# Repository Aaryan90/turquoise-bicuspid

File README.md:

TurquoiseBicuspid
=================

Bluetooth Notification System

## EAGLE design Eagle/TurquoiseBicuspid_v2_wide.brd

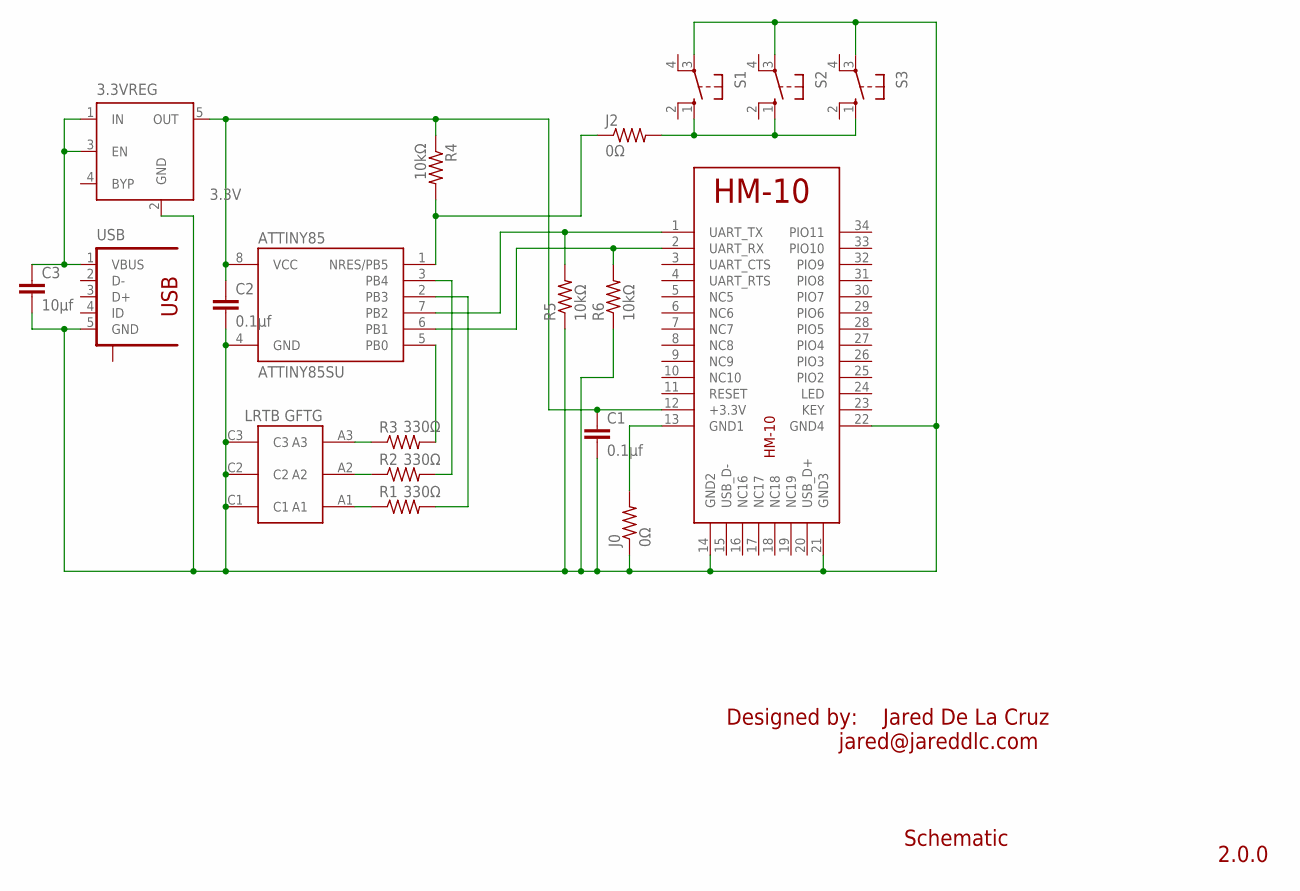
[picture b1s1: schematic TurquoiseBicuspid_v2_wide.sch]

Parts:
3.3VREG: 3.3V; SOT23-5
ATTINY85: ATTINY85SU; ATTINY85
C1, C2: 0.1µf; C1206
C3: 10µf; C1206
HM-10: HM-10BOARD; HM-10
J0, J2: 0Ω; R1206
R1, R2, R3: 330Ω; M1206
R4, R5, R6: 10kΩ; R1206
S1, S2, S3: 10-XX; B3F-10XX
U$1: LRTB_GFTG
USB: 10118192-0001LF

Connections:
3.3V: 3.3VREG.5 (OUT), ATTINY85.8 (VCC), C1.1, C2.1, HM-10.12 (+3.3V), R4.1
5V: 3.3VREG.1 (IN), 3.3VREG.3 (EN), C3.1, USB.1 (VBUS)
A1: ATTINY85.2 (PB3), R1.1, R1.2, U$1.A1
A2: ATTINY85.3 (PB4), R2.1, R2.2, U$1.A2
A3: ATTINY85.5 (PB0), R3.1, R3.2, U$1.A3
BT_RX: ATTINY85.6 (PB1), HM-10.2 (UART_RX), R6.2
BT_TX: ATTINY85.7 (PB2), HM-10.1 (UART_TX), R5.2
GND: 3.3VREG.2 (GND), ATTINY85.4 (GND), C1.2, C2.2, C3.2, HM-10.13 (GND1), HM-10.14 (GND2), HM-10.21 (GND3), HM-10.22 (GND4), J0.1, J0.2, R5.1, R6.1, S1.3, S2.3, S3.3, U$1.C1, U$1.C2, U$1.C3, USB.5 (GND)
RESET: ATTINY85.1 (NRES/PB5), J2.1, J2.2, R4.2, S1.1 (S), S2.1 (S), S3.1 (S)

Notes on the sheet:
2.0.0
Designed by: Jared De La Cruz jared@jareddlc.com
Schematic

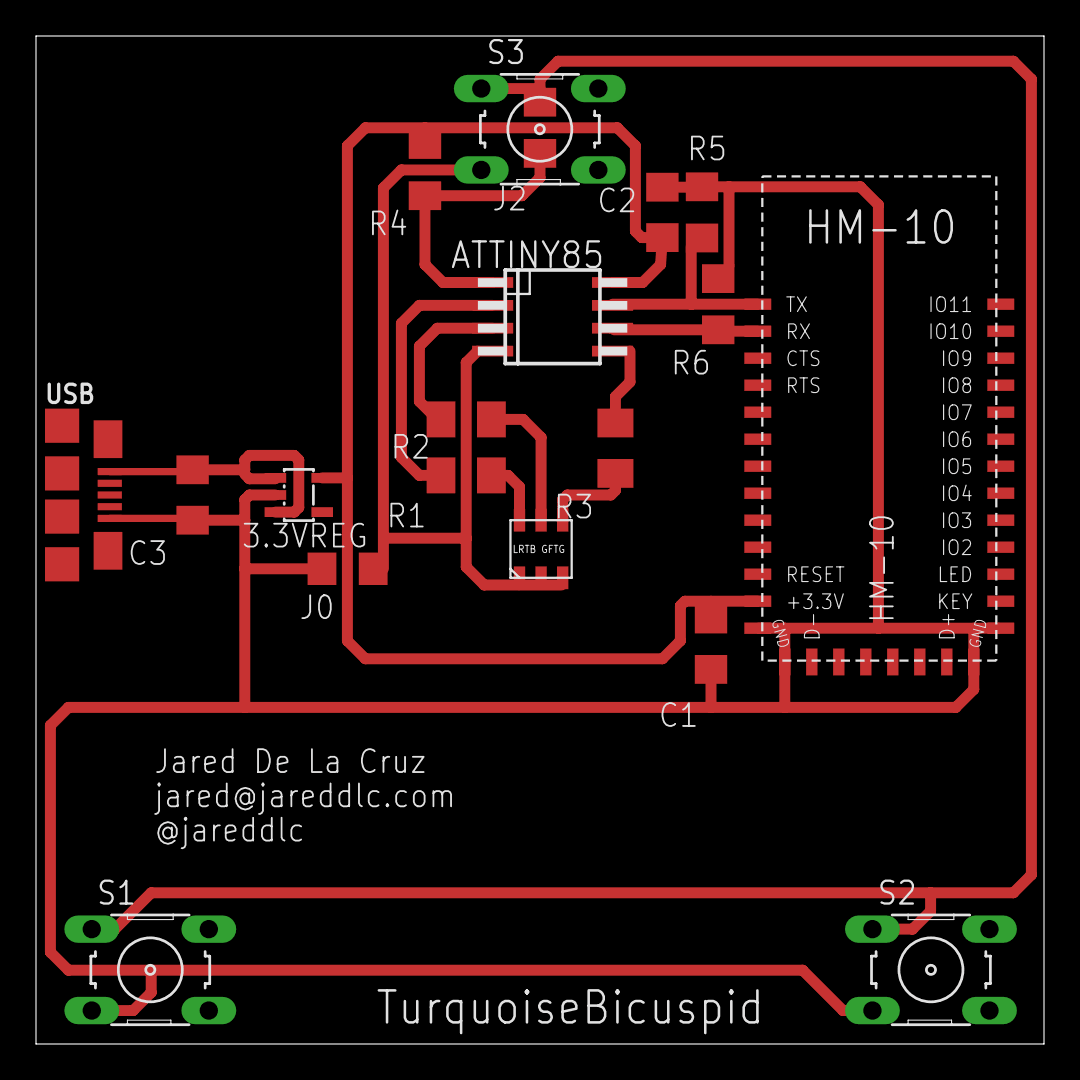
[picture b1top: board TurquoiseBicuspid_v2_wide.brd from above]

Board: 2 copper layers, 56.0 x 56.0 mm, 19 parts (0 on the bottom side), 9 nets.

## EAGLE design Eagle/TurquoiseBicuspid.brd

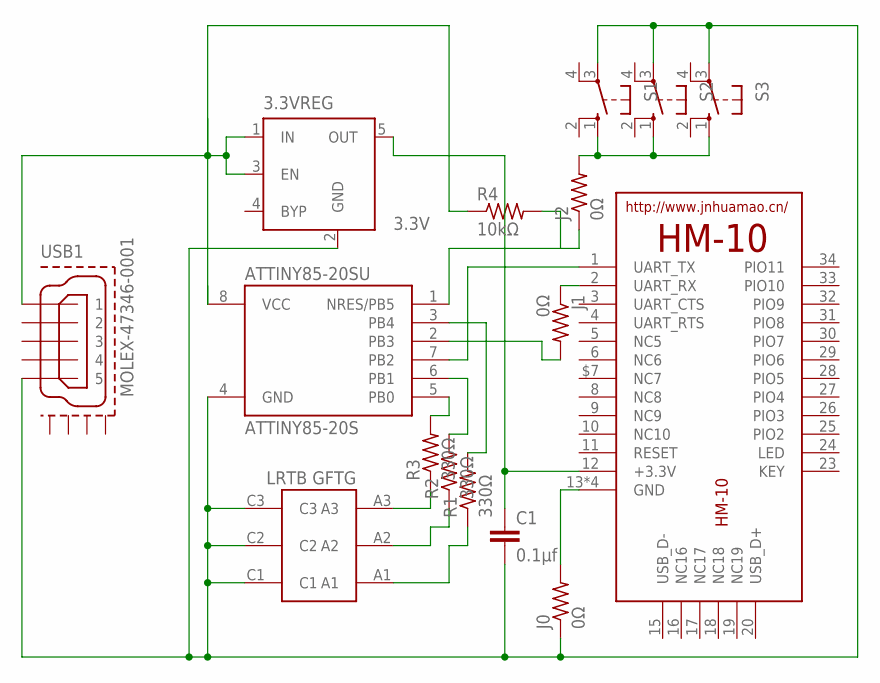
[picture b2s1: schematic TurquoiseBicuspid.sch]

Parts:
3.3VREG: 3.3V; SOT23-5
ATTINY85-20SU: ATTINY85-20S; SOIC8_EIAJ_208MIL
C1: 0.1µf; C1206
HM-10: HM-10-BOARD; 26.9X13X2.2_BOARD
J0, J1, J2: 0Ω; R1206
R1, R2, R3: 330Ω; M1206
R4: 10kΩ; R1206
S1, S2, S3: 10-XX; B3F-10XX
U$1: LRTB_GFTG
USB1: MOLEX-47346-0001; MOLEX-47364-0001

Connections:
3.3V: 3.3VREG.5 (OUT), C1.1, HM-10.12 (+3.3V)
5V: 3.3VREG.1 (IN), 3.3VREG.3 (EN), ATTINY85-20SU.8 (VCC), R4.1, USB1.1
A1: ATTINY85-20SU.3 (PB4), R1.1, R1.2, U$1.A1
A2: ATTINY85-20SU.6 (PB1), R2.1, R2.2, U$1.A2
A3: ATTINY85-20SU.5 (PB0), R3.1, R3.2, U$1.A3
BT_RX: ATTINY85-20SU.2 (PB3), HM-10.2 (UART_RX), J1.1, J1.2
BT_TX: ATTINY85-20SU.7 (PB2), HM-10.1 (UART_TX)
GND: 3.3VREG.2 (GND), ATTINY85-20SU.4 (GND), C1.2, J0.1, S1.3, S2.3, S3.3, U$1.C1, U$1.C2, U$1.C3, USB1.5
unnamed: HM-10.13 (GND), HM-10.14 (GND), HM-10.21 (GND), HM-10.22 (GND), J0.2
RESET: ATTINY85-20SU.1 (NRES/PB5), J2.1, J2.2, R4.2, S1.1 (S), S2.1 (S), S3.1 (S)

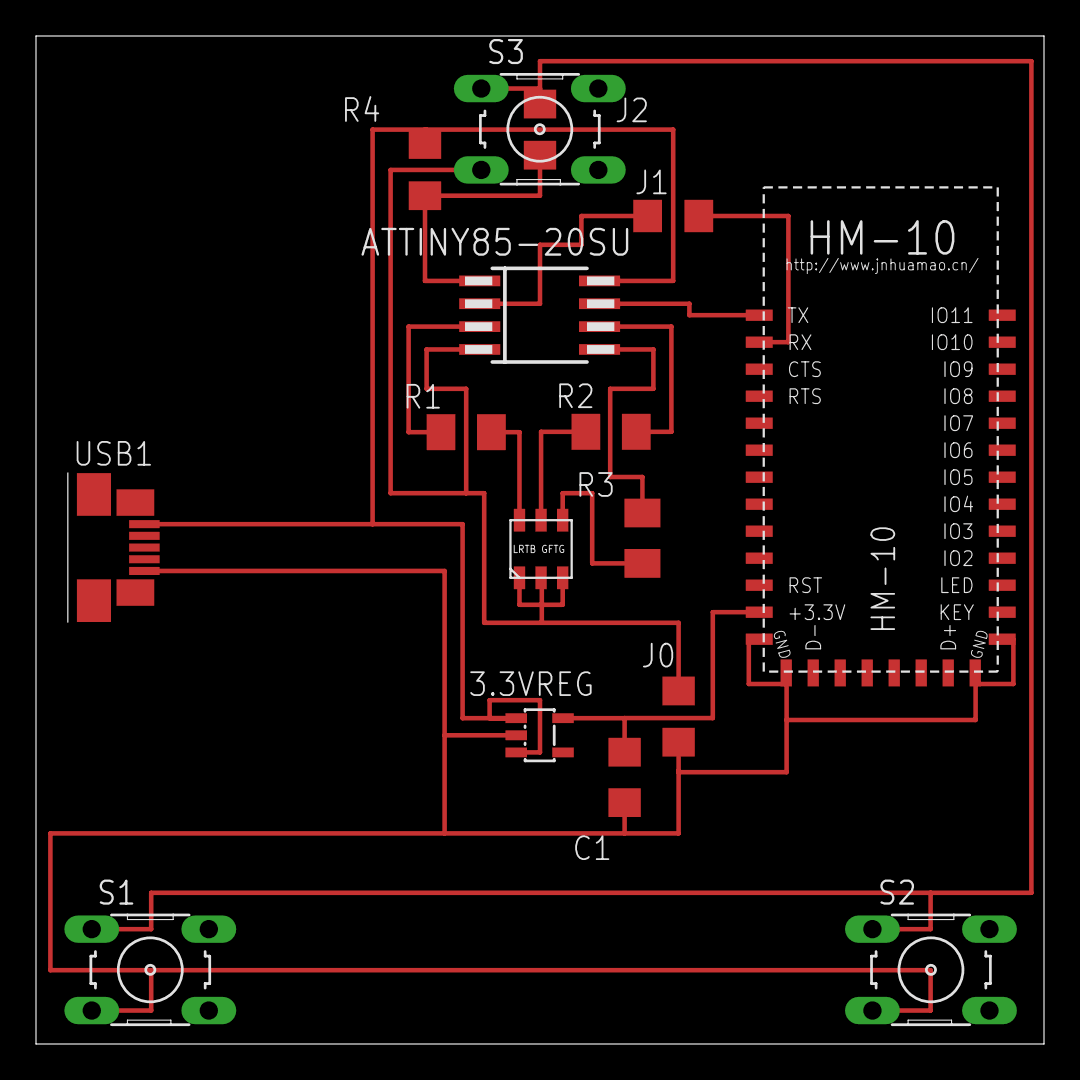
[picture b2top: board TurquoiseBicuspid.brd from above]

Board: 2 copper layers, 56.0 x 56.0 mm, 16 parts (0 on the bottom side), 10 nets.

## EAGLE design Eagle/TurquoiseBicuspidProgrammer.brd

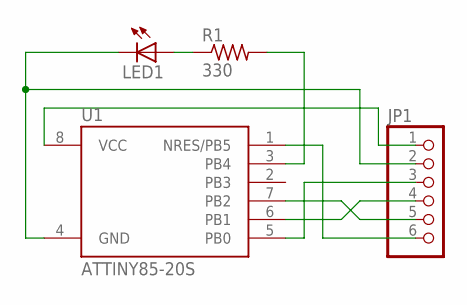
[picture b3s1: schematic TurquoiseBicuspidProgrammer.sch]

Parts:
JP1: PINHD-1X6; 1X06
LED1: LED5MM
R1: 330; 0207/10
U1: ATTINY85-20S; SOIC8_EIAJ_208MIL

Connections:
unnamed: JP1.1, U1.8 (VCC)
unnamed: JP1.2, LED1.K (C), U1.4 (GND)
unnamed: JP1.6, U1.1 (NRES/PB5)
unnamed: JP1.3, U1.5 (PB0)
unnamed: JP1.4, U1.6 (PB1)
unnamed: JP1.5, U1.7 (PB2)
unnamed: R1.2, U1.3 (PB4)
unnamed: LED1.A, R1.1

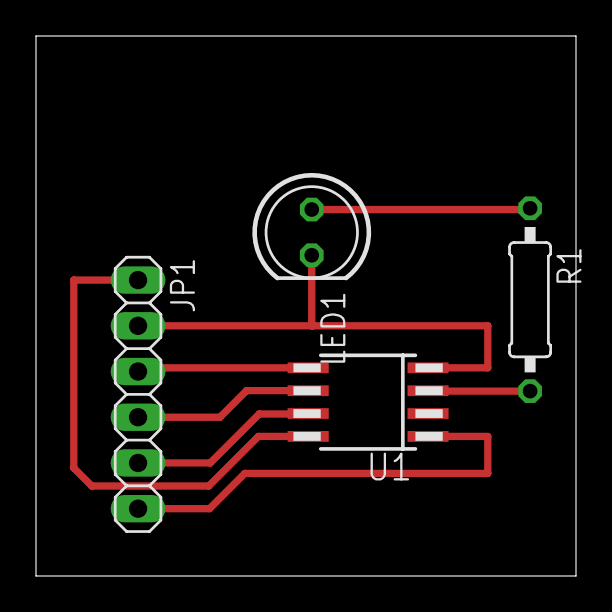
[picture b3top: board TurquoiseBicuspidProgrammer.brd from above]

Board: 2 copper layers, 30.0 x 30.0 mm, 4 parts (0 on the bottom side), 8 nets.

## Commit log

2014-03-10 added toggle LED
2014-03-11 added phone and sms listeners
2014-03-13 added on/off
2014-03-16 moving over to PreferenceFragment
2014-03-17 slowly adding Bluetooth into SettingsActivity
2014-03-19 Implement UI Logic
2014-03-20 more UI logic
2014-03-21 fixed listpreference
2014-03-24 added sms & phone prefs
2014-03-25 added empty service
2014-03-26 added sms and phone listeners to service
2014-03-27 creating SavedPreferences
2014-03-28 needs to rework to prevent leaks
2014-03-30 removed global context
2014-03-31 added sms and phone settings
2014-04-01 changing bt.send() to match arduino.
2014-04-02 added blink loop, settings preview
2014-04-03 added bt to service
2014-04-04 added broadcast to sms
2014-04-04 added broadcast to phone, bt.send() added
2014-04-05 cleaning up file
2014-04-06 comments
2014-04-07 added repeat param to bt.send()
2014-04-08 added proto repeat
2014-04-09 moved repeat to loop()
2014-04-10 removed sms and phone repeat.
2014-04-11 global vars
2014-04-12 added clear repeat in android
2014-04-14 removed settings repeat
2014-04-18 adding "Turn On" preference
2014-04-22 removed old prefs, fixing socket.close()
2014-04-25 added ColorPicker
2014-04-27 added color preferences
2014-04-28 added rgb color to bt.send()
2014-04-30 added color to bt.send()
2014-05-02 set blinkRGB default
2014-05-07 added pulse & pulseRGB
2014-05-12 save correct color and notifyService
2014-05-21 added button clear
2014-07-25 added eagle files
2014-07-28 added resistors and switches
2014-07-30 first attempt at board
2014-07-31 removed 1 switch
2014-08-01 fresh board
2014-08-01 attempt 3
2014-08-07 removed programming headers
2014-08-07 route gnd
2014-08-11 added programmer board
2014-09-03 fixed 5v
2014-09-09 board v1.1
2014-10-15 Attempting BLE
2014-10-29 Trying to create BLE Service
2014-10-30 update BLE bindService
2014-10-31 Fix BLE bindService
2014-11-03 reworking BLE service
2014-11-06 need to rework restorePreferences
2014-11-12 connect to BLE working?
2014-11-13 added BLE send()
2014-11-14 fixed first start bug, BLE arduino
2014-11-15 Rearranged PCB silk screen
2014-11-15 PCB added name
2014-11-19 Arduino files for ATtiny
2014-12-03 cleaned preferences, BT enable timeout
2014-12-05 connect preference
2014-12-10 attempt at BLE scan
2014-12-11 BLE scan set
2014-12-12 BLE scanned and paired in one list
2014-12-15 added BitSmang
2014-12-16 send BitSmang bytes[]
2014-12-17 arduino BitSmang
2014-12-19 arduino parse BitSmang
2014-12-19 open source license
2015-01-05 added hardware functions, renamed loop to number
2015-01-13 Arduino tiny update
2015-01-19 btSerial.print() fix
2015-02-18 Started new revision of board
2015-02-19 added frame
2015-02-20 fixed pulldown resistor
2015-02-25 connecting routes
2015-03-18 Android app defaults and bug fix
2015-03-19 force connection
2015-03-20 arduino switch BT rx,tx pins
2015-03-24 re-routed pins for RX & TX
2015-03-25 board design v2
2015-03-30 added miter bends
2015-03-31 added wide version of board
2015-03-31 .6mm to .4mm usb
2015-04-15 Change pins for v2 PCB
2015-04-23 Cleaning code
2015-06-09 Enclosure

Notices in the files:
parts and their libraries:
fci_micro_usb: Copyright (C) 2008, Bob Starr
